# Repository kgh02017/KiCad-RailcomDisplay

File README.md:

# KiCad-RailcomDisplay

KiCad6 project files for RailcomDisplay

## Description

This repository contains KiCad6 project files for RailcomDisplay. 

The RailcomDisplay is a local detector that displays data transmitted from RailCom supported decoders.

The schematic of RailcomDisplay is based on greate work of [Paco's Official Web Site](https://usuaris.tinet.cat/fmco/railcom_en.html#rdisplay)

## Artifacts

- [Schematic](./artifacts/RailcomDisplay-schematic.pdf)
- [BOM](https://htmlview.glitch.me/?https://github.com/kgh02017/KiCad-RailcomDisplay/blob/main/project/RailcomDisplay/bom/RailcomDisplay.html)

## Additional Info

The documentation and firmware of RailcomDisplay can be downloaded from [Paco's Official Web Site's download page](https://usuaris.tinet.cat/fmco/download_en.html).

### Documentation

-  [Manual](https://usuaris.tinet.cat/fmco/download/RailComDisplay_manual.pdf)

### Firmware of PIC16F690

-  [Firmware](https://usuaris.tinet.cat/fmco/download/RailComDisplay.zip)

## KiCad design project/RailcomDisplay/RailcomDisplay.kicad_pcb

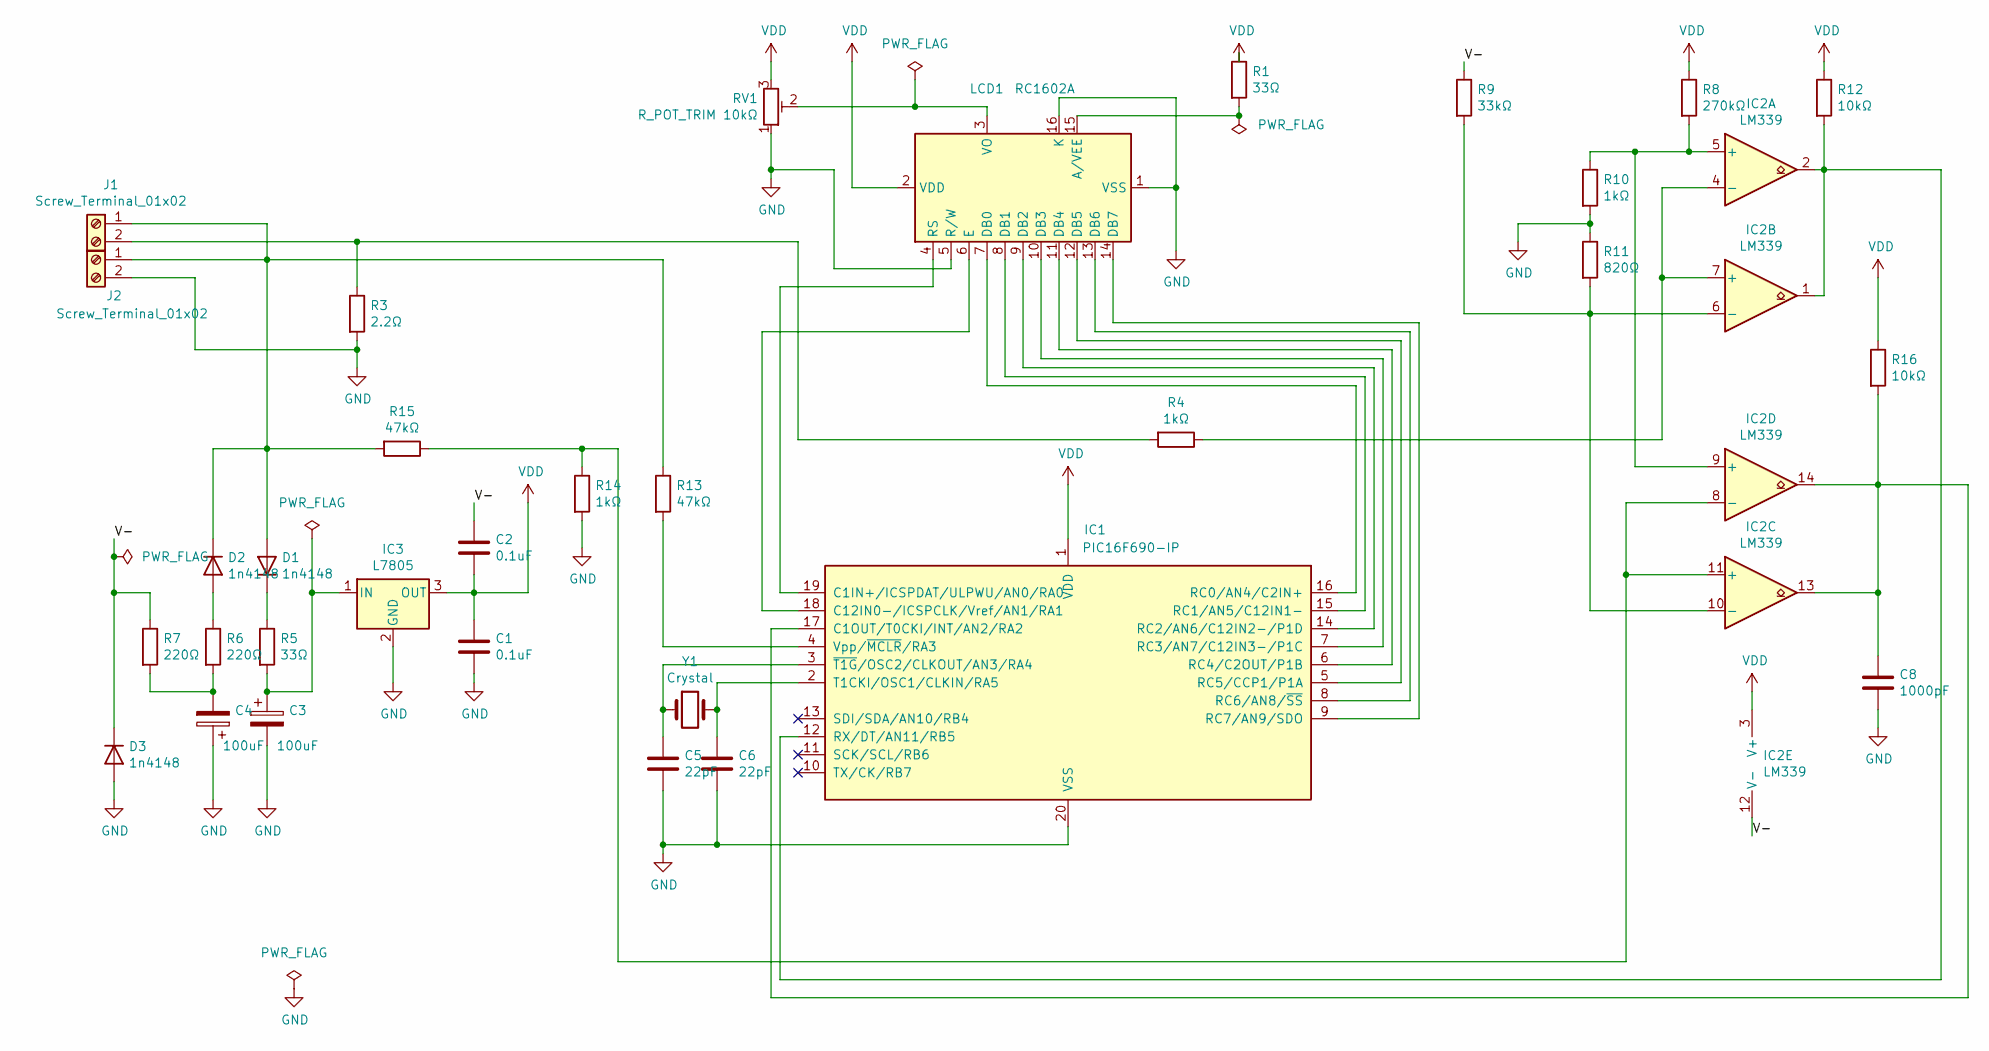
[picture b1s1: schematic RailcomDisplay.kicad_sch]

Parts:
C1, C2: 0.1uF; C_Disc_D3.0mm_W1.6mm_P2.50mm
C3, C4: 100uF; CP_Radial_D5.0mm_P2.00mm
C5, C6: 22pF; C_Disc_D3.0mm_W1.6mm_P2.50mm
C8: 1000pF; C_Disc_D3.0mm_W1.6mm_P2.50mm
D1, D2, D3: 1n4148; D_DO-35_SOD27_P7.62mm_Horizontal
IC1: PIC16F690-IP; DIP-20_W7.62mm_Socket
IC2: LM339; DIP-14_W7.62mm_Socket
IC3: L7805; L7805_TO-220_Horizontal_TabUp
J1, J2: Screw_Terminal_01x02; PhoenixContact_MC_1,5_2-G-3.81_1x02_P3.81mm_Horizontal
LCD1: RC1602A; WC1602A
R1, R5: 33Ω; R_Axial_DIN0207_L6.3mm_D2.5mm_P7.62mm_Horizontal
R3: 2.2Ω; R_Axial_DIN0207_L6.3mm_D2.5mm_P7.62mm_Horizontal
R4, R10, R14: 1kΩ; R_Axial_DIN0207_L6.3mm_D2.5mm_P7.62mm_Horizontal
R6, R7: 220Ω; R_Axial_DIN0207_L6.3mm_D2.5mm_P7.62mm_Horizontal
R8: 270kΩ; R_Axial_DIN0207_L6.3mm_D2.5mm_P7.62mm_Horizontal
R9: 33kΩ; R_Axial_DIN0207_L6.3mm_D2.5mm_P7.62mm_Horizontal
R11: 820Ω; R_Axial_DIN0207_L6.3mm_D2.5mm_P7.62mm_Horizontal
R12, R16: 10kΩ; R_Axial_DIN0207_L6.3mm_D2.5mm_P7.62mm_Horizontal
R13, R15: 47kΩ; R_Axial_DIN0207_L6.3mm_D2.5mm_P7.62mm_Horizontal
RV1: R_POT_TRIM 10kΩ; Potentiometer_Bourns_3296W_Vertical
Y1: Crystal; Resonator-2Pin_W10.0mm_H5.0mm

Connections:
/V-: C2.1, D3.1 (K), IC2.12 (V-), R7.1, R9.1
GND: C1.2, C3.2, C4.1, C5.2, C6.2, C8.2, D3.2 (A), IC1.20 (VSS), IC3.2 (GND), J2.2, LCD1.1 (VSS), LCD1.5 (R/W), LCD1.16 (K), R3.2, R10.2, R11.1, R14.2, RV1.1
unnamed: C3.1, IC3.1 (IN), R5.2
unnamed: C4.2, R6.2, R7.2
unnamed: C5.1, IC1.3 (~T1G/OSC2/CLKOUT/AN3/RA4), Y1.1
unnamed: C6.1, IC1.2 (T1CKI/OSC1/CLKIN/RA5), Y1.2
unnamed: C8.1, IC1.17 (C1OUT/T0CKI/INT/AN2/RA2), IC2.13, IC2.14, R16.2
unnamed: D1.1 (K), R5.1
unnamed: D1.2 (A), D2.1 (K), J1.1, J2.1, R13.1, R15.2
unnamed: D2.2 (A), R6.1
unnamed: IC1.4 (Vpp/~MCLR/RA3), R13.2
unnamed: IC1.5 (RC5/CCP1/P1A), LCD1.12 (DB5)
unnamed: IC1.6 (RC4/C2OUT/P1B), LCD1.11 (DB4)
unnamed: IC1.7 (RC3/AN7/C12IN3-/P1C), LCD1.10 (DB3)
unnamed: IC1.8 (RC6/AN8/~SS), LCD1.13 (DB6)
unnamed: IC1.9 (RC7/AN9/SDO), LCD1.14 (DB7)
unnamed: IC1.12 (RX/DT/AN11/RB5), IC2.1, IC2.2, R12.2
unnamed: IC1.14 (RC2/AN6/C12IN2-/P1D), LCD1.9 (DB2)
unnamed: IC1.15 (RC1/AN5/C12IN1-), LCD1.8 (DB1)
unnamed: IC1.16 (RC0/AN4/C2IN+), LCD1.7 (DB0)
unnamed: IC1.18 (C12IN0-/ICSPCLK/Vref/AN1/RA1), LCD1.6 (E)
unnamed: IC1.19 (C1IN+/ICSPDAT/ULPWU/AN0/RA0), LCD1.4 (RS)
unnamed: IC2.4 (-), IC2.7 (+), R4.1
unnamed: IC2.5 (+), IC2.9 (+), R8.2, R10.1
unnamed: IC2.6 (-), IC2.10 (-), R9.2, R11.2
unnamed: IC2.8 (-), IC2.11 (+), R14.1, R15.1
unnamed: J1.2, R3.1, R4.2
unnamed: LCD1.3 (VO), RV1.2
unnamed: LCD1.15 (A/VEE), R1.2
VDD: C1.1, C2.2, IC1.1 (VDD), IC2.3 (V+), IC3.3 (OUT), LCD1.2 (VDD), R1.1, R8.1, R12.1, R16.1, RV1.3

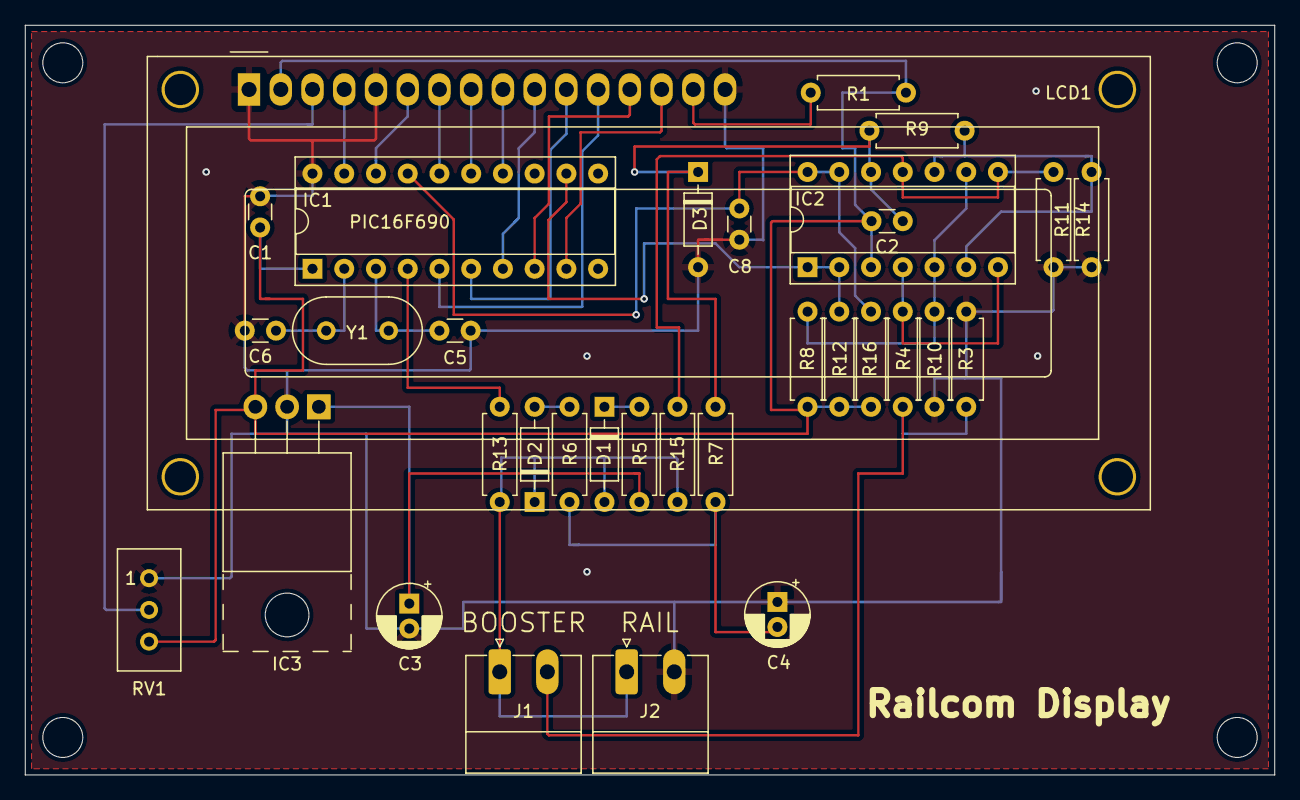
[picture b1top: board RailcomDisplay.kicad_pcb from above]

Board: 2 copper layers, 100.0 x 60.0 mm, 37 parts (0 on the bottom side), 30 nets.

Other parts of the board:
MH1, MH2, MH3, MH4: MountingHole_3.2mm_M3

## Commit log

2022-11-22 Add KiCad6 project files for RailcomDisplay
2022-11-23 Add .gitattributes This patch adds .gitattributes so that GitHub can recognize this repository as KiCad project.
